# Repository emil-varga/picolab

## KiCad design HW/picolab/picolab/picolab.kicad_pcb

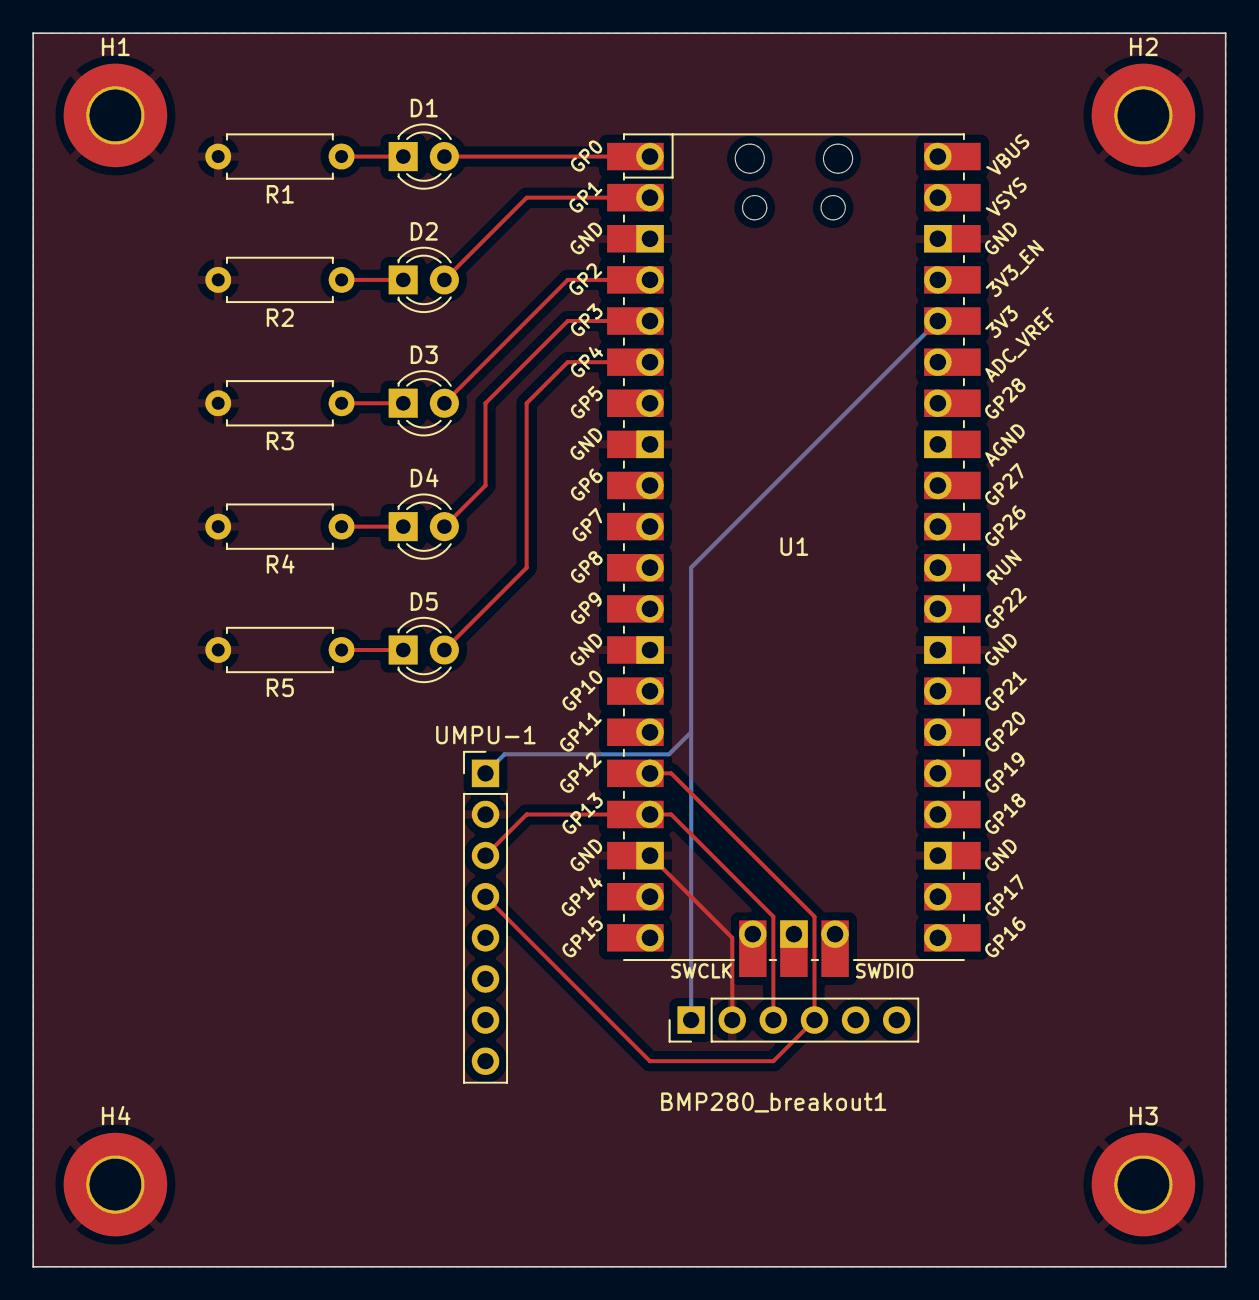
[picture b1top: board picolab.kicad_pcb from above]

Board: 2 copper layers, 73.7 x 76.2 mm, 17 parts (0 on the bottom side), 14 nets.

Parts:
BMP280_breakout1: PinHeader_1x06_P2.54mm_Vertical
D1, D2, D3, D4, D5: LED; LED_D3.0mm
H1, H2, H3, H4: MountingHole_Pad; MountingHole_3.2mm_M3_Pad_TopBottom
R1, R2, R3, R4, R5: R; R_Axial_DIN0207_L6.3mm_D2.5mm_P7.62mm_Horizontal
U1: Pico; RPi_Pico_SMD_TH
UMPU-1: PinHeader_1x08_P2.54mm_Vertical

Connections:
GND: BMP280_breakout1.2 (GND), H1.1, H2.1, H3.1, H4.1, R1.2, R2.2, R3.2, R4.2, R5.2, U1.3 (GND), U1.8 (GND), U1.13 (GND), U1.18 (GND), U1.23 (GND), U1.28 (GND), U1.38 (GND), UMPU-1.2 (GND)
unnamed: BMP280_breakout1.3 (SCL), U1.17 (GPIO13), UMPU-1.3 (SCL)
unnamed: BMP280_breakout1.4 (SDA), U1.16 (GPIO12), UMPU-1.4 (SDA)
unnamed: BMP280_breakout1.1 (VCC), U1.36 (3V3), UMPU-1.1 (VCC)
unnamed: D1.2 (A), U1.1 (GPIO0)
unnamed: D1.1 (K), R1.1
unnamed: D2.2 (A), U1.2 (GPIO1)
unnamed: D2.1 (K), R2.1
unnamed: D3.2 (A), U1.4 (GPIO2)
unnamed: D3.1 (K), R3.1
unnamed: D4.2 (A), U1.5 (GPIO3)
unnamed: D4.1 (K), R4.1
unnamed: D5.2 (A), U1.6 (GPIO4)
unnamed: D5.1 (K), R5.1

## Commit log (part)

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2022-11-27 start on scpi parsing, basic tokenizing of input strings
2022-12-01 basic command parsing, blinking turning few pins on and off through SCPI
2022-12-01 fast sampling adc based on sdk examples
2022-12-03 spi communication with bmp280 based on the sdk example, works but code is somewhat messy
2022-12-03 error message for unknown commands
2024-11-06 gitignore
2024-11-06 change communication with the BMP280 from SPI to I2C
2024-11-07 accelerometer and gyro readout
2024-11-15 include stdlib
2024-12-02 minor changes, update to Pico 2 W
2025-01-10 kicad project files
2025-10-14 Switch to vs code pico extension and minor fixes.
